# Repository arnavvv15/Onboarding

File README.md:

# EcoCar Onboarding Board – STM32F103

A 2-layer STM32F103 (LQFP48) development board designed in KiCad 10 as the onboarding project for the University of Alberta Eco Car Club. The design follows Phil's Lab's STM32 PCB tutorial and adds LEDs, buttons, a potentiometer, a buzzer and breakout headers.

## Features

- **MCU:** STM32F103 in LQFP48 (U1), with an external HSE crystal (Y1)
- **Power:** USB-C (J1) → AMS1117-3.3 LDO (U2) → 3.3 V, with a ferrite bead (FB1) filtering VDDA and a red power LED (D1)
- **USB:** Full-speed USB on PA11/PA12, with 5.1 kΩ CC pull-downs (R2, R3) so USB-C chargers supply 5 V
- **Programming:** SWD header (J2), BOOT0 switch (SW1)
- **User I/O:** 10 LEDs, 3 push buttons (SW2–SW4), 10 kΩ potentiometer (RV1) on the ADC, buzzer (BZ3), 4 PWM outputs
- **Headers:** UART (J4), I2C with 1.5 kΩ pull-ups (J3), SPI2 (J5), power out (J6: VBUS, 3.3 V, GND)
- **PCB:** 2 layers, GND pour on both layers

## Pin map (main signals)

| Function | Pin | Port |
|---|---|---|
| Potentiometer (ADC) | 10 | PA0 |
| BTN1 / BTN2 | 11 / 12 | PA1 / PA2 |
| BTN3 | 20 | PB2 |
| LED1 / LED2 | 14 / 15 | PA4 / PA5 |
| LED3 / LED6 | 29 / 30 | PA8 / PA9 |
| LED4 / LED5 | 38 / 41 | PA15 / PB5 |
| PWM1 / PWM2 | 16 / 17 | PA6 / PA7 |
| PWM3 / PWM4 | 18 / 19 | PB0 / PB1 |
| I2C (J3) | 21 / 22 | PB10 / PB11 |
| SPI2 CS / SCK / MISO / MOSI (J5) | 25 / 26 / 27 / 28 | PB12 / PB13 / PB14 / PB15 |
| UART (J4) | 42 / 43 | PB6 / PB7 |
| USB D− / D+ | 32 / 33 | PA11 / PA12 |
| SWDIO / SWCLK (J2) | 34 / 37 | PA13 / PA14 |
| Buzzer | 45 | PB8 |

See `Onboarding.kicad_sch` for the full schematic.

## Repository contents

| File | Description |
|---|---|
| `Onboarding.kicad_pro` / `.kicad_sch` / `.kicad_pcb` | KiCad project, schematic and board |
| `Onboarding-*.gbr`, `Onboarding-job.gbrjob` | Gerber files |
| `Onboarding-PTH.drl`, `Onboarding-NPTH.drl` | Drill files |
| `EcoOnboard_FW/` | Firmware |

## Design notes

- Minimum track width is 0.15 mm, and copper-to-board-edge clearance is 0.3 mm.
- BTN3 is on PB2 (BOOT1). That's safe as long as BOOT0 is low during normal boot.
- DRC shows no unconnected items. The remaining warnings are courtyard overlaps and silkscreen.

## Tools

KiCad 10.0

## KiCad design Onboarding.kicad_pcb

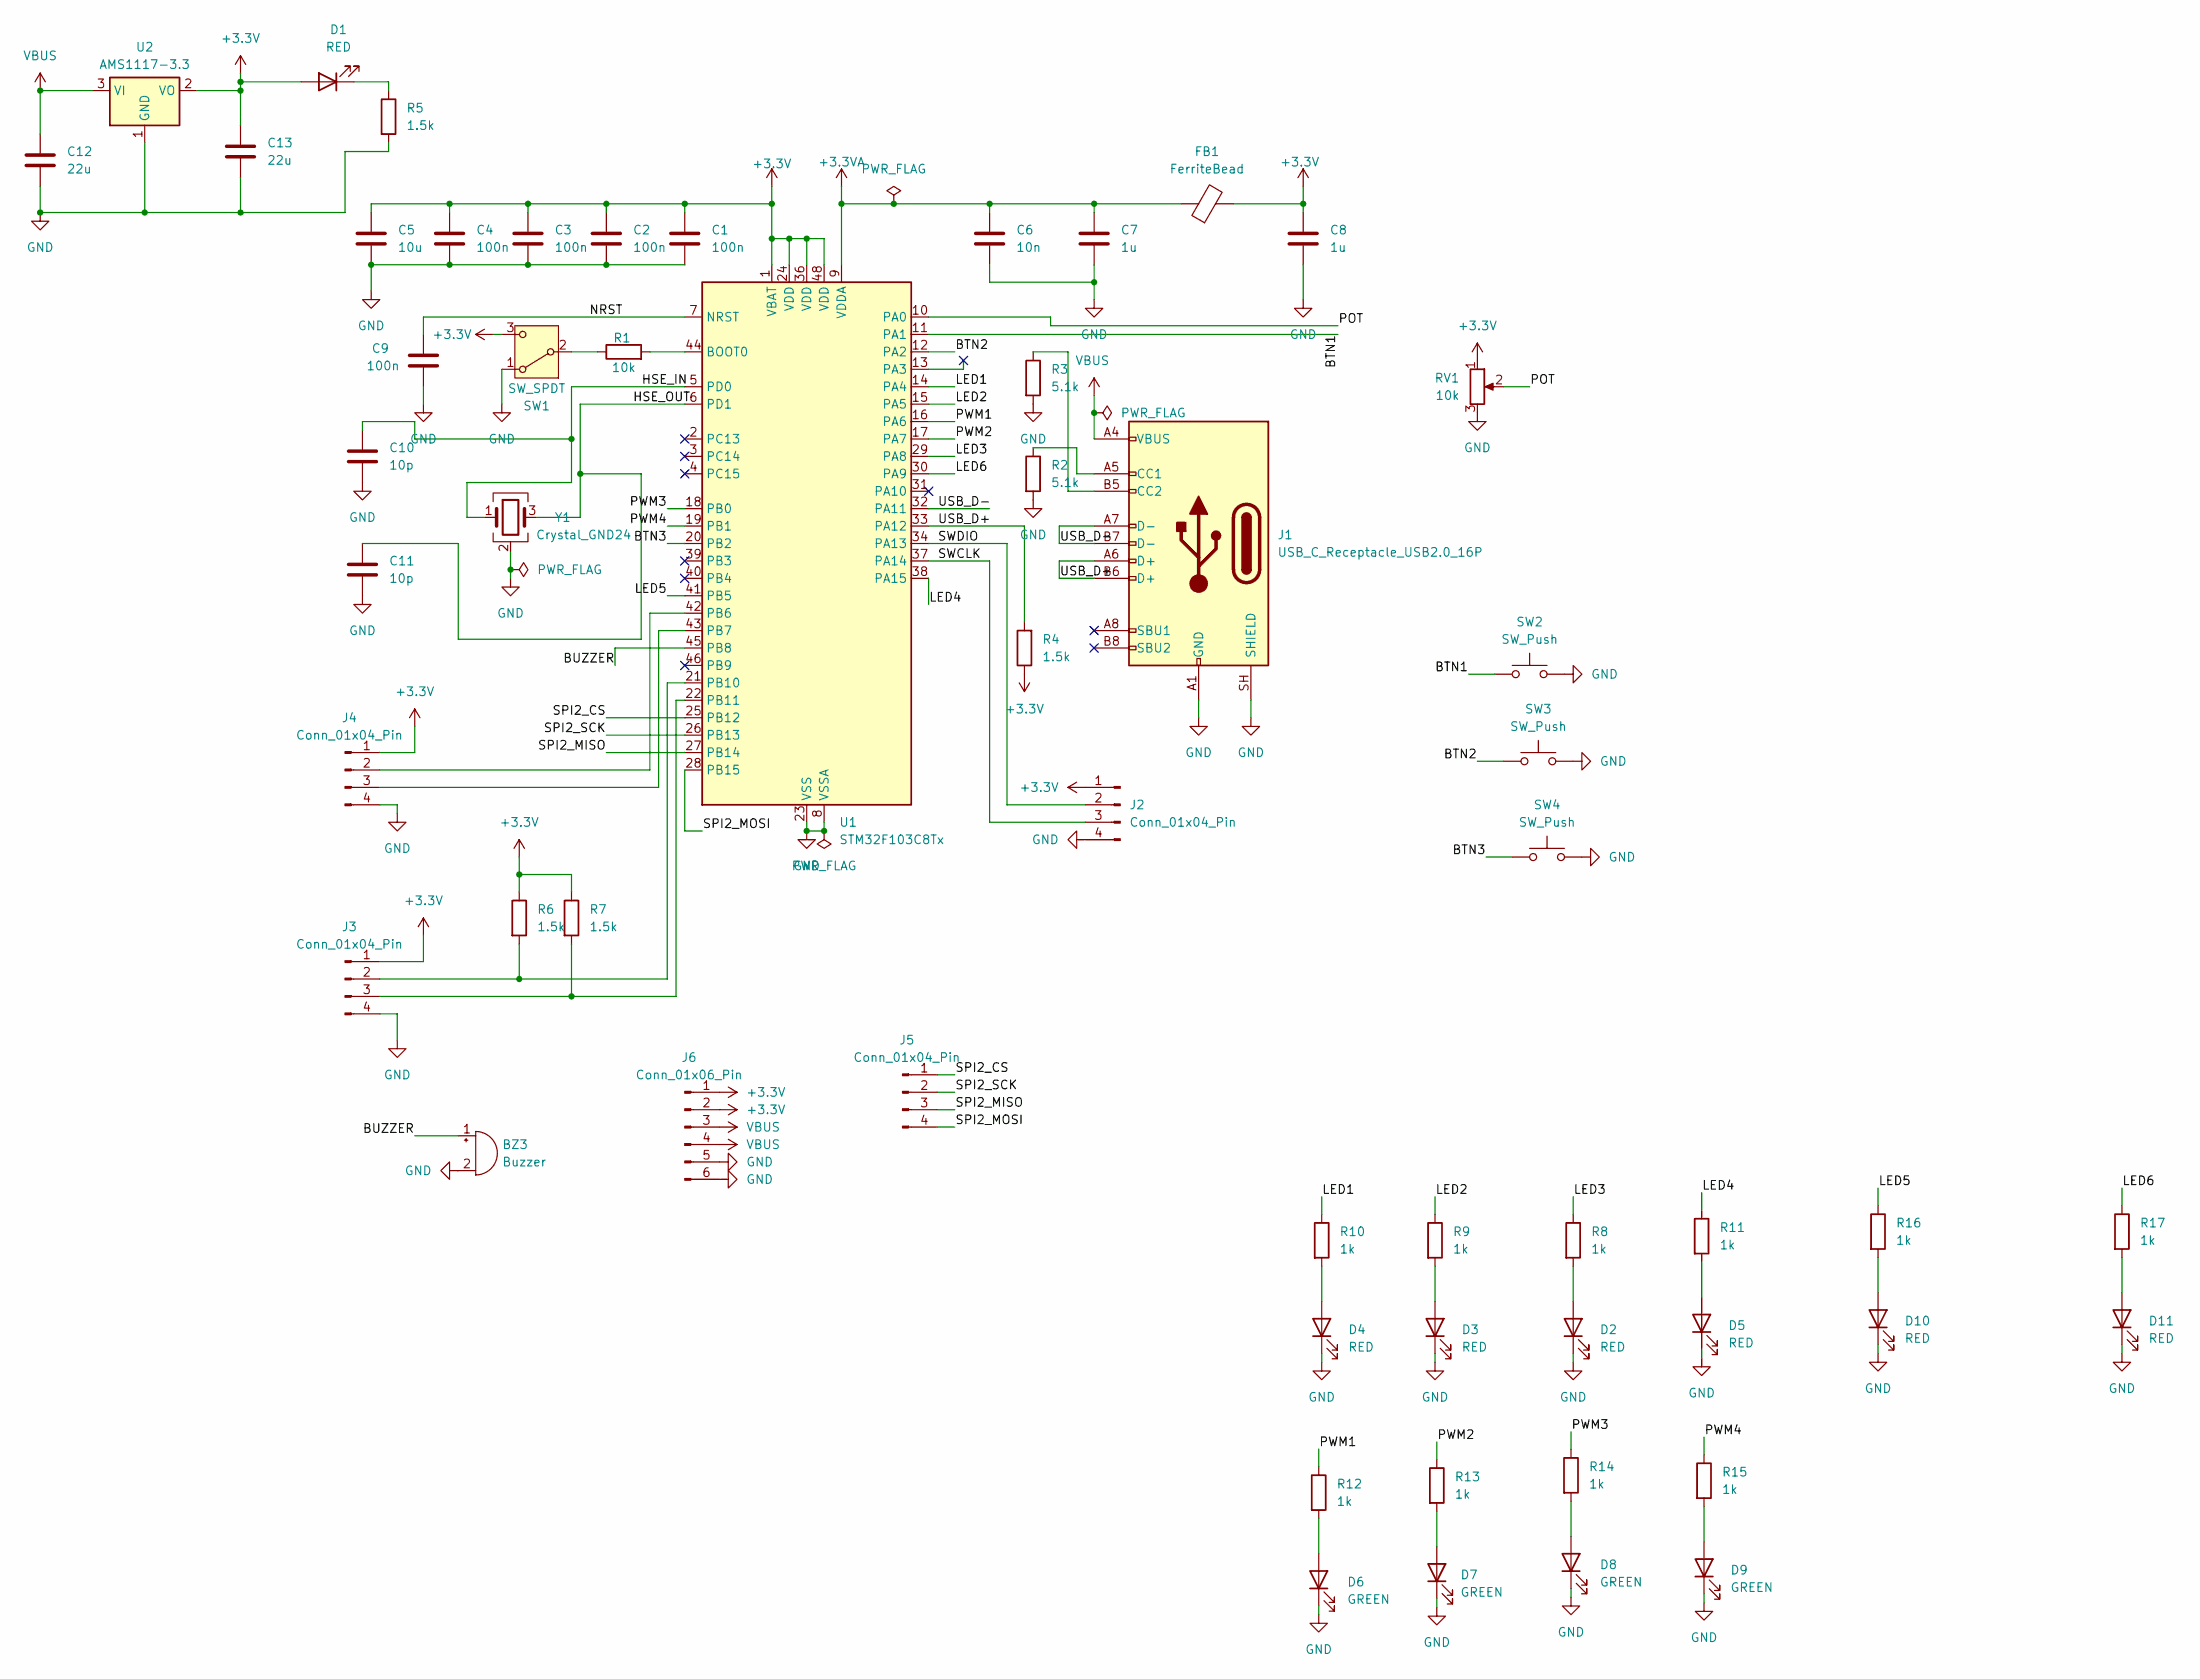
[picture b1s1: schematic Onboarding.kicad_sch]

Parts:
BZ3: Buzzer; Buzzer_12x9.5RM7.6
C1, C2, C3, C4, C9: 100n; C_0603_1608Metric
C5: 10u; C_0805_2012Metric
C6: 10n; C_0603_1608Metric
C7, C8: 1u; C_0603_1608Metric
C10, C11: 10p; C_0603_1608Metric
C12, C13: 22u; C_0805_2012Metric
D1, D2, D3, D4, D5, D10, D11: RED; LED_0603_1608Metric
D6, D7, D8, D9: GREEN; LED_0603_1608Metric
FB1: FerriteBead; L_0603_1608Metric
J1: USB_C_Receptacle_USB2.0_16P; USB_C_Receptacle_HRO_TYPE-C-31-M-12
J2, J3, J4, J5: Conn_01x04_Pin; PinHeader_1x04_P2.54mm_Vertical
J6: Conn_01x06_Pin; PinHeader_1x06_P2.54mm_Vertical
R1: 10k; R_0603_1608Metric
R2, R3: 5.1k; R_0603_1608Metric
R4, R5, R6, R7: 1.5k; R_0603_1608Metric
R8, R9, R10, R11, R12, R13, R14, R15, R16, R17: 1k; R_0603_1608Metric
RV1: 10k; Potentiometer_Bourns_3386P_Vertical
SW1: SW_SPDT; SW_Slide_SPDT_Straight_CK_OS102011MS2Q
SW2, SW3, SW4: SW_Push; SW_PUSH_6mm
U1: STM32F103C8Tx; LQFP-48_7x7mm_P0.5mm
U2: AMS1117-3.3; SOT-223-3_TabPin2
Y1: Crystal_GND24; Crystal_SMD_3225-4Pin_3.2x2.5mm

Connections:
+3.3V: C1.1, C2.1, C3.1, C4.1, C5.1, C8.1, C13.1, D1.2 (A), FB1.2, J2.1, J3.1, J4.1, J6.1, J6.2, R4.1, R6.1, R7.1, RV1.1, SW1.3 (C), U1.1 (VBAT), U1.24 (VDD), U1.36 (VDD), U1.48 (VDD), U2.2 (VO)
+3.3VA: C6.1, C7.1, FB1.1, U1.9 (VDDA)
/BTN1: SW2.1, U1.11 (PA1)
/BTN2: SW3.1, U1.12 (PA2)
/BTN3: SW4.1, U1.20 (PB2)
/BUZZER: BZ3.1 (+), U1.45 (PB8)
/HSE_IN: C10.1, U1.5 (PD0), Y1.1
/HSE_OUT: C11.1, U1.6 (PD1), Y1.3
/LED1: R10.1, U1.14 (PA4)
/LED2: R9.1, U1.15 (PA5)
/LED3: R8.1, U1.29 (PA8)
/LED4: R11.1, U1.38 (PA15)
/LED5: R16.1, U1.41 (PB5)
/LED6: R17.1, U1.30 (PA9)
/NRST: C9.1, U1.7 (NRST)
/POT: RV1.2, U1.10 (PA0)
/PWM1: R12.1, U1.16 (PA6)
/PWM2: R13.1, U1.17 (PA7)
/PWM3: R14.1, U1.18 (PB0)
/PWM4: R15.1, U1.19 (PB1)
/SPI2_CS: J5.1, U1.25 (PB12)
/SPI2_MISO: J5.3, U1.27 (PB14)
/SPI2_MOSI: J5.4, U1.28 (PB15)
/SPI2_SCK: J5.2, U1.26 (PB13)
/SWCLK: J2.3, U1.37 (PA14)
/SWDIO: J2.2, U1.34 (PA13)
/USB_D+: J1.A6 (D+), J1.B6 (D+), R4.2, U1.33 (PA12)
/USB_D-: J1.A7 (D-), J1.B7 (D-), U1.32 (PA11)
GND: BZ3.2 (-), C1.2, C2.2, C3.2, C4.2, C5.2, C6.2, C7.2, C8.2, C9.2, C10.2, C11.2, C12.2, C13.2, D2.1 (K), D3.1 (K), D4.1 (K), D5.1 (K), D6.1 (K), D7.1 (K), D8.1 (K), D9.1 (K), D10.1 (K), D11.1 (K), J1.A1 (GND), J1.A12 (GND), J1.B1 (GND), J1.B12 (GND), J1.SH (SHIELD), J2.4, J3.4, J4.4, J6.5, J6.6, R2.2, R3.2, R5.2, RV1.3, SW1.1 (A), SW2.2, SW3.2, SW4.2, U1.8 (VSSA), U1.23 (VSS), U1.35 (VSS), U1.47 (VSS), U2.1 (GND), Y1.2 (G), Y1.4 (G)
unnamed: D1.1 (K), R5.1
unnamed: D2.2 (A), R8.2
unnamed: D3.2 (A), R9.2
unnamed: D4.2 (A), R10.2
unnamed: D5.2 (A), R11.2
unnamed: D6.2 (A), R12.2
unnamed: D7.2 (A), R13.2
unnamed: D8.2 (A), R14.2
unnamed: D9.2 (A), R15.2
unnamed: D10.2 (A), R16.2
unnamed: D11.2 (A), R17.2
unnamed: J1.A5 (CC1), R2.1
unnamed: J1.B5 (CC2), R3.1
unnamed: J3.2, R6.2, U1.21 (PB10)
unnamed: J3.3, R7.2, U1.22 (PB11)
unnamed: J4.2, U1.42 (PB6)
unnamed: J4.3, U1.43 (PB7)
unnamed: R1.1, SW1.2 (B)
unnamed: R1.2, U1.44 (BOOT0)
VBUS: C12.1, J1.A4 (VBUS), J1.A9 (VBUS), J1.B4 (VBUS), J1.B9 (VBUS), J6.3, J6.4, U2.3 (VI)

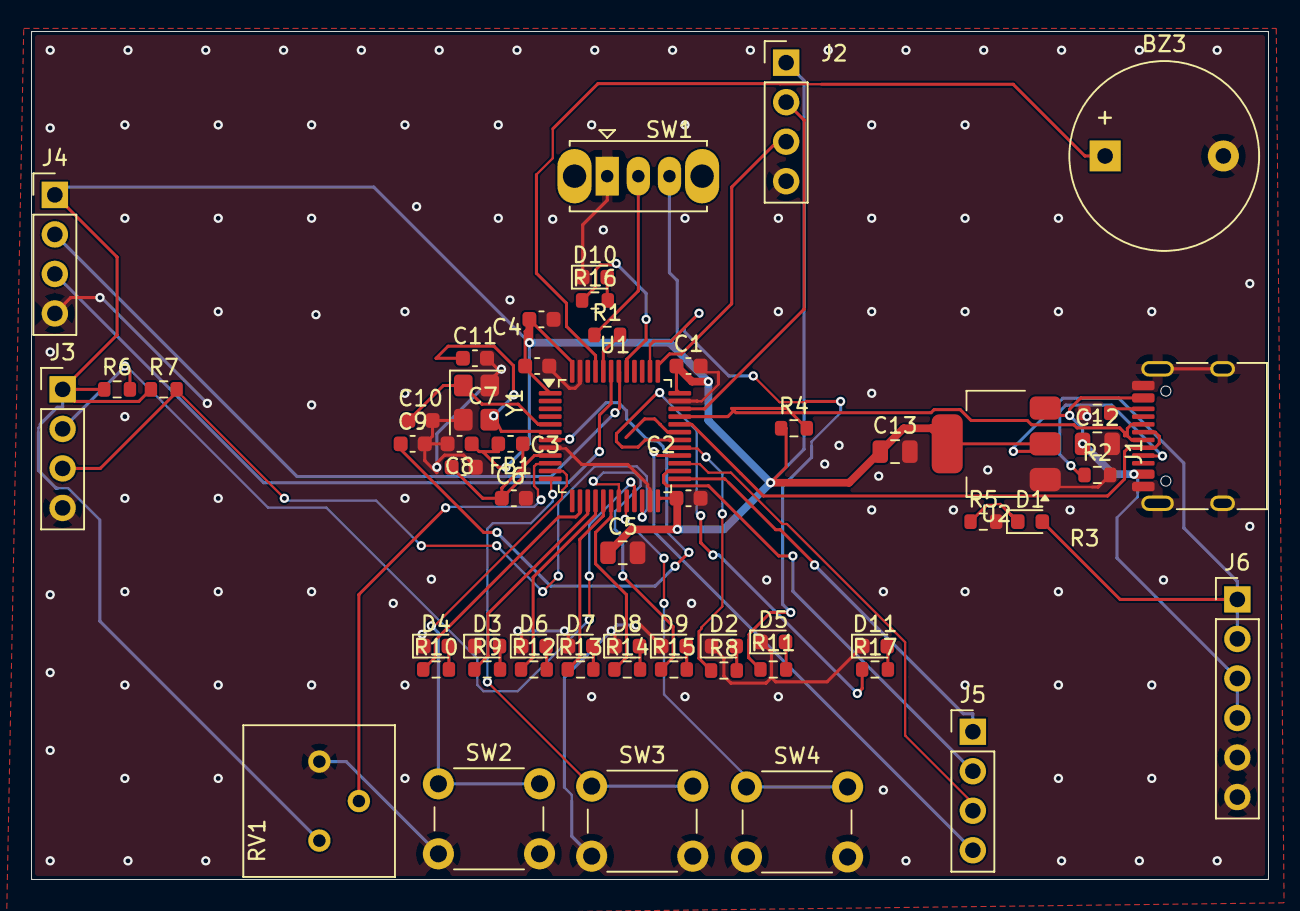
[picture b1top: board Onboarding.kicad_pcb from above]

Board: 2 copper layers, 79.5 x 54.5 mm, 57 parts (0 on the bottom side), 49 nets.

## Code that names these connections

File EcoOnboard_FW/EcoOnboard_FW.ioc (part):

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Mcu.Name=STM32F103C(8-B)Tx
Mcu.Package=LQFP48
Mcu.UserName=STM32F103C8Tx
PA0-WKUP.GPIOParameters=GPIO_Label
PA0-WKUP.GPIO_Label=POT
PA0-WKUP.Signal=ADCx_IN0
PA1.GPIOParameters=GPIO_PuPd,GPIO_Label
PA1.GPIO_Label=BTN1
PA1.GPIO_PuPd=GPIO_PULLUP
PA1.Signal=GPIO_Input
PA10.Mode=Asynchronous
PA10.Signal=USART1_RX
PA11.Mode=Device
PA11.Signal=USB_DM
PA12.Mode=Device
PA12.Signal=USB_DP
PA13.Mode=Serial_Wire
PA13.Signal=SYS_JTMS-SWDIO
PA14.Mode=Serial_Wire
PA14.Signal=SYS_JTCK-SWCLK
PA15.GPIOParameters=GPIO_Label
PA15.GPIO_Label=LED4
PA15.Signal=GPIO_Output
PA2.GPIOParameters=GPIO_PuPd,GPIO_Label
PA2.GPIO_Label=BTN2
PA2.GPIO_PuPd=GPIO_PULLUP
PA2.Signal=GPIO_Input
PA3.GPIOParameters=GPIO_PuPd,GPIO_Label
PA3.GPIO_Label=BTN3
PA3.GPIO_PuPd=GPIO_PULLUP
PA3.Signal=GPIO_Input
PA4.GPIOParameters=GPIO_Label
PA4.GPIO_Label=LED1
PA4.Signal=GPIO_Output
PA5.GPIOParameters=GPIO_Label
PA5.GPIO_Label=LED2
PA5.Signal=GPIO_Output
PA6.Signal=S_TIM3_CH1
PA7.Signal=S_TIM3_CH2
PA8.GPIOParameters=GPIO_Label
PA8.GPIO_Label=LED3
PA8.Signal=GPIO_Output
PA9.Mode=Asynchronous
PA9.Signal=USART1_TX
PB0.Signal=S_TIM3_CH3
PB1.Signal=S_TIM3_CH4
PB10.Mode=I2C
PB10.Signal=I2C2_SCL
PB11.Mode=I2C
PB11.Signal=I2C2_SDA
PB12.GPIOParameters=GPIO_Label
PB12.GPIO_Label=SPI2_CS
PB12.Signal=GPIO_Output
PB13.Mode=Full_Duplex_Master
PB13.Signal=SPI2_SCK
PB14.Mode=Full_Duplex_Master
PB14.Signal=SPI2_MISO
PB15.Mode=Full_Duplex_Master
PB15.Signal=SPI2_MOSI
PB5.GPIOParameters=GPIO_Label
PB5.GPIO_Label=LED5
PB5.Signal=GPIO_Analog
PB6.Mode=I2C
PB6.Signal=I2C1_SCL
PB7.Mode=I2C
PB7.Signal=I2C1_SDA
PB9.GPIOParameters=GPIO_Label
PB9.GPIO_Label=LED6
PB9.Signal=GPIO_Output
PD0-OSC_IN.Mode=HSE-External-Oscillator
PD0-OSC_IN.Signal=RCC_OSC_IN
PD1-OSC_OUT.Mode=HSE-External-Oscillator
PD1-OSC_OUT.Signal=RCC_OSC_OUT
RCC.SYSCLKFreq_VALUE=72000000
RCC.SYSCLKSource=RCC_SYSCLKSOURCE_PLLCLK
board=custom
